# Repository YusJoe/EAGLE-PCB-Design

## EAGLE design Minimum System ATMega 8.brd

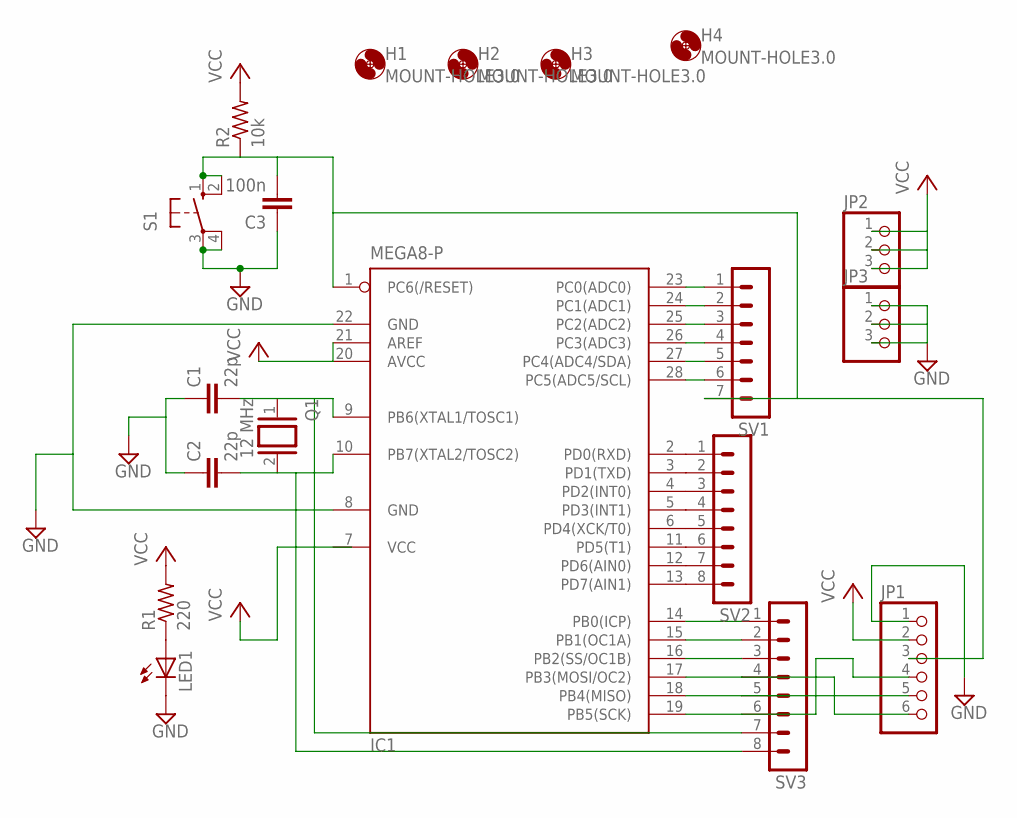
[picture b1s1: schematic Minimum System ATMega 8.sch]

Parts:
C1, C2: 22p; C025-030X050
C3: 100n; C025-030X050
H1, H2, H3, H4: MOUNT-HOLE3.0; 3,0
IC1: MEGA8-P; DIL28-3
JP1: PINHD-1X6/90; 1X06/90
JP2, JP3: PINHD-1X3; 1X03
LED1: LED3MM
Q1: 12 MHz; QS
R1: 220; 0204/7
R2: 10k; 0204/7
S1: 10-XX; B3F-10XX
SV1: MA07-1
SV2, SV3: MA08-1

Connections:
GND: C1.1, C2.1, C3.1, IC1.8 (GND), IC1.22 (GND), JP1.1, JP3.1, JP3.2, JP3.3, LED1.K (C), S1.3, S1.4 (P1)
MISO: IC1.18 (PB4(MISO)), JP1.5, SV3.5
MOSI: IC1.17 (PB3(MOSI/OC2)), JP1.6, SV3.4
unnamed: IC1.23 (PC0(ADC0)), SV1.1
unnamed: IC1.24 (PC1(ADC1)), SV1.2
unnamed: IC1.25 (PC2(ADC2)), SV1.3
unnamed: IC1.26 (PC3(ADC3)), SV1.4
unnamed: IC1.27 (PC4(ADC4/SDA)), SV1.5
unnamed: IC1.28 (PC5(ADC5/SCL)), SV1.6
unnamed: IC1.2 (PD0(RXD)), SV2.1
unnamed: IC1.3 (PD1(TXD)), SV2.2
unnamed: IC1.4 (PD2(INT0)), SV2.3
unnamed: IC1.5 (PD3(INT1)), SV2.4
unnamed: IC1.6 (PD4(XCK/T0)), SV2.5
unnamed: IC1.11 (PD5(T1)), SV2.6
unnamed: IC1.12 (PD6(AIN0)), SV2.7
unnamed: IC1.13 (PD7(AIN1)), SV2.8
unnamed: IC1.14 (PB0(ICP)), SV3.1
unnamed: IC1.15 (PB1(OC1A)), SV3.2
unnamed: IC1.16 (PB2(SS/OC1B)), SV3.3
unnamed: C1.2, IC1.9 (PB6(XTAL1/TOSC1)), Q1.1, SV3.7
unnamed: C3.2, IC1.1 (PC6(/RESET)), JP1.3, R2.1, S1.1 (S), S1.2 (S1), SV1.7
unnamed: IC1.19 (PB5(SCK)), JP1.4, SV3.6
unnamed: C2.2, IC1.10 (PB7(XTAL2/TOSC2)), Q1.2, SV3.8
unnamed: LED1.A, R1.1
VCC: IC1.7 (VCC), IC1.20 (AVCC), IC1.21 (AREF), JP1.2, JP2.1, JP2.2, JP2.3, R1.2, R2.2

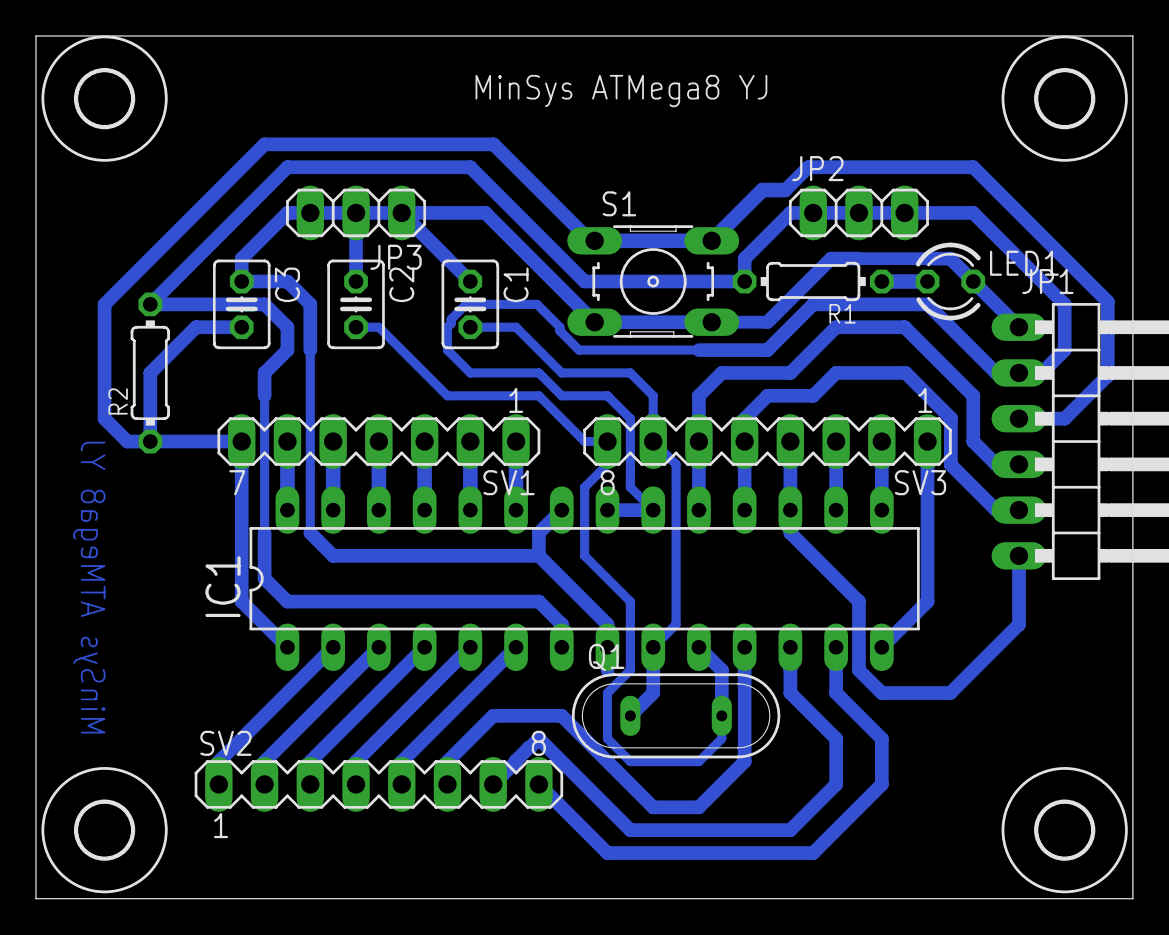
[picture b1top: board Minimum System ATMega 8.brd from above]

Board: 2 copper layers, 60.9 x 47.9 mm, 19 parts (0 on the bottom side), 26 nets.
